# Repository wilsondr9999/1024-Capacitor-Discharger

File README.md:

# Capacitor Discharger

This project is a passive (unpowered) capacitor discharger that can safely discharge capacitors up to 450V and 1000 uF.  It assists the operator in quickly discharging the capacitor and providing visual feedback of the discharging process and its completion.

## Overview

The capacitor discharger is a handheld unit with 2 LEDs for indication, and two standard shrouded test lead ports on one end.  It's purpose is to allow safe discharge of a capacitor that is in-circuit prior to working on that circuit.  Capacitors can hold a charge, sometimes for a long period of time, and in some circuits the amount of energy they can hold is dangerous, even potentially lethal.

This unit allows the operator to touch two test leads to the capacitor terminals, and the unit will allow the capacitor to discharge at a constant rate of 125 mA.  This is sufficient current to discharge the largest capacitor that is recommended to be discharged with this unit (a capacitor rated up to 450V, and up to 1000 uF of capacitance) within about 15 seconds.

## Principle of Operation

The unit is a passive device, i.e. it is not powered and no batteries or power source is needed.  The energy in the capacitor is used to light the indicator LEDs during the discharge.

A fixed resistance bank is used to allow the capacitor to discharge at a constant current of 125 mA.  The capacitor's energy is dumped into 11 resistors rated at 5W each.

One LED (yellow) lights as the capacitor is discharging.  This LED will remain lit until the capacitor has no more energy (usually when it's voltage is less than 2V).

The other LED (red) lights if the capacitor voltage is above 30V.  This LED will extinguish when the capacitor has discharged to less than 30V, indicating that the capacitor would be safe to touch.  An IGBT transistor is used in a specific configuration to drive the >30V LED.

## Instructions for Use

Attach two test leads to the 4mm jacks on the end of the unit.  The unit does not have a polarity restriction, and can discharge capacitors in both orientations.  It is recommended that your test leads are of a type that are rated for at least the working voltage of the capacitor you intend to discharge.  If the voltage is greater than 50V, it is recommended to use high voltage test leads with a category rating of at least CAT I / 600V.

For voltages greater than 50V, use appropriate personal protective equipment (PPE), including electrical safety gloves and safety glasses.

With appropriate personal safety equipment in place, touch the test leads to the capacitor leads in either orientation.  The unit will begin discharging the capacitor, and you will see the yellow discharging LED light up.  The red >30V LED will also light if the capacitor voltage is currently greater than 30V.

Keep the test leads connected to the capacitor until the >30V LED light extinguished.  Once the >30V LED light is extinguished, the capacitor is safe to work with.  If the work requires as close to zero charge in the capacitor as possible, continue holding the test leads connected to the capacitor until the discharge LED light is dim or extinguished.

## Assembly

Gerber files are available in the [1024 Capacitor Discharger](KiCAD%20Project%20-%20Discharger/Fabrication%20Exports/1024%20Capacitor%20Discharger.zip) folder.  The [1024 Capacitor Discharger](KiCAD%20Project%20-%20Discharger/Fabrication%20Exports/1024%20Capacitor%20Discharger.zip) file is a pre-compressed archive that is ready to upload to Oshpark.

All parts needed are listed in the [BOM](KiCAD%20Project%20-%20Discharger/BOM/BOM%201024%20Capacitor%20Discharger.csv) CSV file.

If you want to use a solder stencil for reflow of the SMD components, Osh Stencils can produce this stencil from the [1024 Capacitor Discharger-F_Paste](KiCAD%20Project%20-%20Discharger/Fabrication%20Exports/1024%20Capacitor%20Discharger-F_Paste.gbr) Gerber file.  Select a Stainless Steel 4 mil stencil with a border size of 0.75 inches.  The Solder Stencil Jig is designed to fit this stencil.

Use the [SSJv2 1024 Capacitor Discharger](FreeCAD%20Project/Solder%20Stencil%20Jig%20V2/SSJv2%201024%20Capacitor%20Discharger.stl) file to print the solder stencil jig.  A .3mf file is included if you use PrusaSlicer.  Otherwise use the .stl file with the following settings:

- 0.2 mm layer height
- 3 perimeters
- 4 solid layers on bottom
- 5 solid layers on top
- 20% infill
- No supports required

Solder the SMD components onto the PCB using the stencil + solder paste + reflow, or hand solder them.

Solder the THT components onto the PCB by hand.  Be careful when bending the IGBT legs, they need to be accurate because the hole in the TO-220 case must align with the heat sink and the hole in the PCB.  It is recommended to solder the 4mm PCB-mount Banana jacks while the board is fitted into the case top.  This will ensure that the Banana jacks are perfectly aligned and will not impede the fitting of the PCB in the case.

There is a [ResistorBender](FreeCAD%20Project/1024%20Capacitor%20Discharger%20Case/ResistorBender.stl) file in the 1024 Capacitor Discharge Case directory, this can be optionally printed to properly and uniformly bend the resistor legs to fit the PCB.

When assembling the IGBT heat sink, the stackup should be (from the top down):

- M3x8 button-head screw
- Screw insulator
- TO-220 IGBT
- Thermal grease/compound
- Mica insulator sheet from the TO-220 mounting kit listed in the BOM
- Thermal grease/compound
- Aluminum heat sink
- PCB
- (Back of PCB) Flat Washer
- (Back of PCB) M3 hex nut

The screw that is supplied with the TO-220 mounting kit is too long to fit properly in the printed case.  Replace this screw and nut with a button head M3x8 screw, and use the flat washer and an M3 hex nut on the back of the PCB.  Do not use the lock washer.  This should clear the printed case when assembled.

The Mica insulator sheet may be slightly too large to fit inside the aluminum heat sink.  It can be trimmed with scissors.

Use the [CaseBottom](FreeCAD%20Project/1024%20Capacitor%20Discharger%20Case/CaseBottom.stl) and [CaseTop](FreeCAD%20Project/1024%20Capacitor%20Discharger%20Case/CaseTop.stl) files to print the case, using the same settings as the solder stencil jig.  Use a soldering iron to insert 4 Heat-Set Inserts into the case top.  The Heat-Set Inserts should be an M3 x 6mm size.  The screws used to assembly the case should be an M3x12 with a hex cap head.

Assemble the case halves together with the PCB inside, and insert the 4 hex cap M3x12 screws and tighten.

## License

This project is licensed under two restrictive licenses:

The hardware design is licensed under the CERN Open Hardware Licence Version 2 - Strongly Reciprocal.

The documentation, images, and instructions are licensed under the Creative Commons Attribution-ShareAlike 4.0 International Public License.

As stated by the licenses, all uses of this project require attribution and require open-source release under the same licenses.

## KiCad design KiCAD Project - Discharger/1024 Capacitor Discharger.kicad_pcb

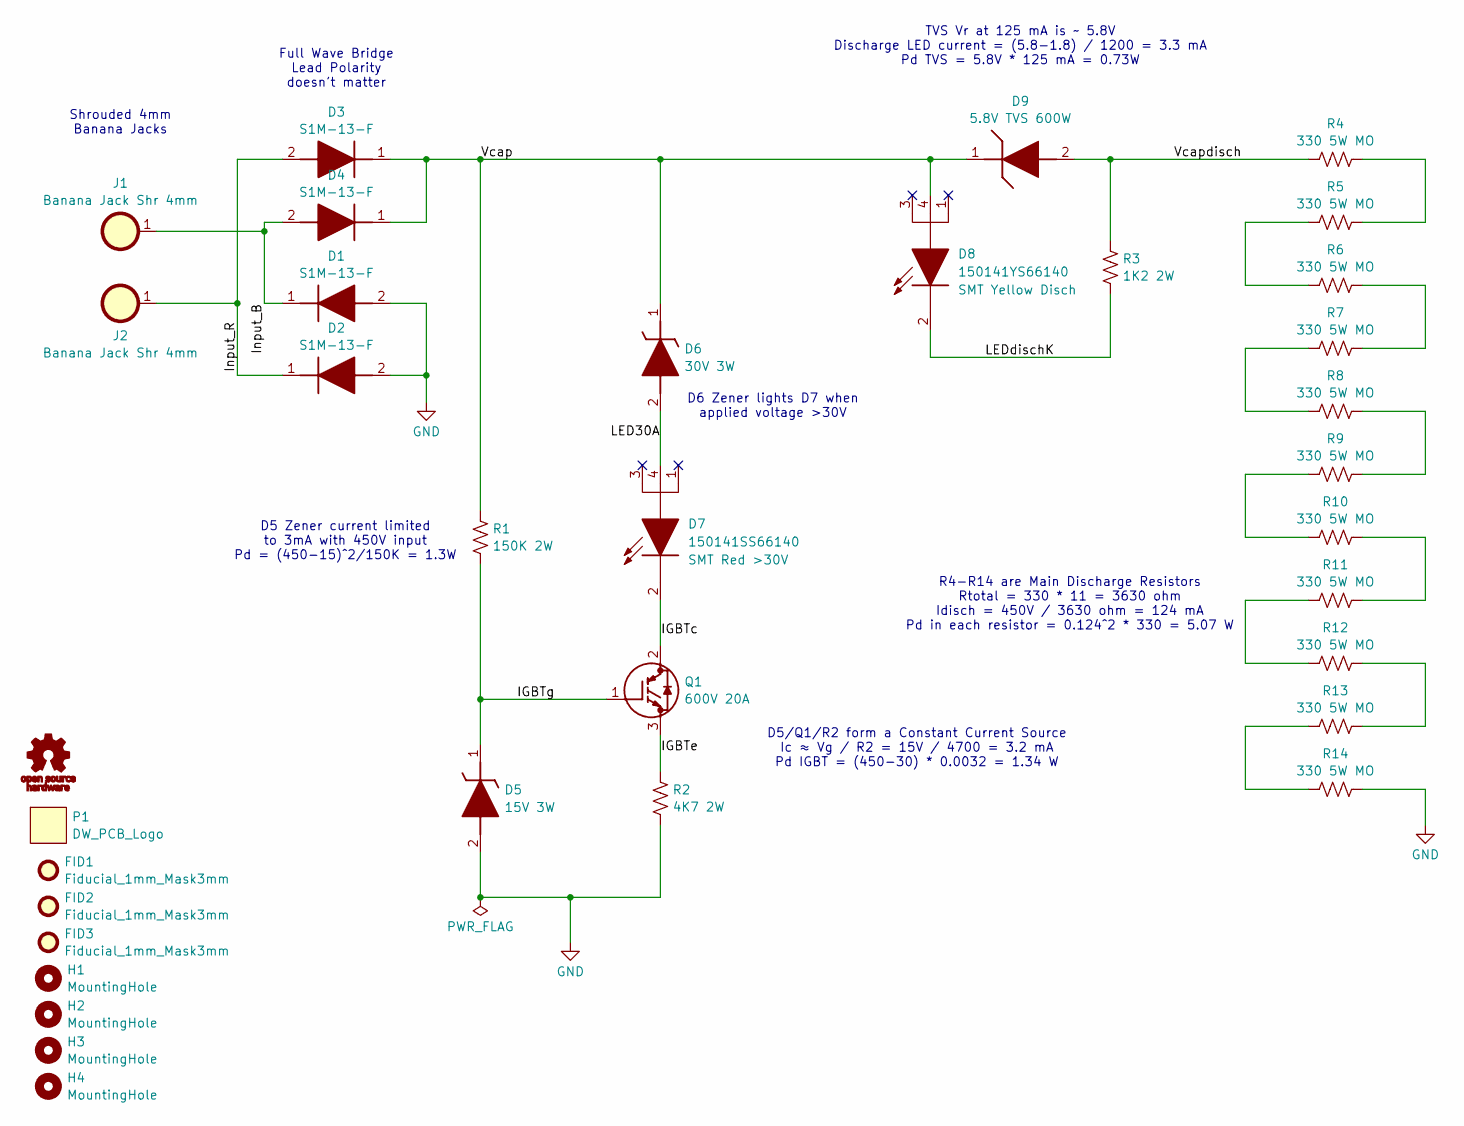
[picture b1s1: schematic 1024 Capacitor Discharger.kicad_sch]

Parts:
D1, D2, D3, D4: S1M-13-F; [D] Diodes Inc S1M-F; Mouser Part Number 621-S1M-F
D5: 1SMB5929BT3G; [D] OnSemi Zener DIOM5436X247N; Mouser Part Number 863-1SMB5929BT3G
D6: 1SMB5936BT3G; [D] OnSemi Zener DIOM5436X247N; Mouser Part Number 863-1SMB5936BT3G
D7: 150141SS66140; [D] Wurth Elektronik 150141SS66140; Mouser Part Number 710-150141SS66140
D8: 150141YS66140; [D] Wurth Elektronik 150141SS66140; Mouser Part Number 710-150141YS66140
D9: 5.8V TVS 600W; [D] Nexperia TVS UniDir PMEG3050EP115; Mouser Part Number 771-PTVS3V3P1UTP,115
FID1, FID2, FID3: Fiducial_1mm_Mask3mm
G1: OSHW_Logo
H1, H2, H3, H4: MountingHole; MountingHole_3.2mm_M3
J1, J2: Banana Jack Shr 4mm; [J] CalTestElec CT3151SP-X; Manufacturer_Part_Number CT3151SP-X; Mouser Part Number 510-CT3151SP-4
P1: DW_PCB_Logo
Q1: 600V 20A; [Q] Infineon IKP20N60T IGBT with ATS-PCB1069 Heat Sink; Mouser Part Number 726-IKP20N60T
R1: 150K 2W; R_2512_6332Metric; Manufacturer_Part_Number CRGP2512F150K; Mouser Part Number 279-CRGP2512F150K
R2: 4K7 2W; R_2512_6332Metric; Manufacturer_Part_Number CRGP2512F4K7; Mouser Part Number 279-CRGP2512F4K7
R3: 1K2 2W; R_2512_6332Metric; Manufacturer_Part_Number CRGP2512F1K2; Mouser Part Number 279-CRGP2512F1K2
R4, R5, R6, R7, R8, R9, R10, R11, R12, R13, R14: 330 5W MO; [R] TE Connectivity MO Res 5W; Manufacturer_Part_Number ROX5SSJ330R; Mouser Part Number 279-ROX5SSJ330R

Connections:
/IGBTc: D7.2 (K), Q1.2 (C)
/IGBTe: Q1.3 (E), R2.1
/IGBTg: D5.1 (K), Q1.1 (G), R1.2
/Input_B: D1.1 (K), D4.2 (A), J1.1
/Input_R: D2.1 (K), D3.2 (A), J2.1
/LED30A: D6.2 (A), D7.4 (A2)
/LEDdischK: D8.2 (K), R3.2
/Vcap: D3.1 (K), D4.1 (K), D6.1 (K), D8.4 (A2), D9.1 (K), R1.1
/Vcapdisch: D9.2 (A), R3.1, R4.1
GND: D1.2 (A), D2.2 (A), D5.2 (A), R2.2, R14.2
unnamed: R4.2, R5.2
unnamed: R5.1, R6.1
unnamed: R6.2, R7.2
unnamed: R7.1, R8.1
unnamed: R8.2, R9.2
unnamed: R9.1, R10.1
unnamed: R10.2, R11.2
unnamed: R11.1, R12.1
unnamed: R12.2, R13.2
unnamed: R13.1, R14.1

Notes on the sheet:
Full Wave Bridge Lead Polarity doesn't matter
R4-R14 are Main Discharge Resistors Rtotal = 330 * 11 = 3630 ohm Idisch = 450V / 3630 ohm = 124 mA Pd in each resistor = 0.124^2 * 330 = 5.07 W
TVS Vr at 125 mA is ~ 5.8V Discharge LED current = (5.8-1.8) / 1200 = 3.3 mA Pd TVS = 5.8V * 125 mA = 0.73W
D5/Q1/R2 form a Constant Current Source Ic ≈ Vg / R2 = 15V / 4700 = 3.2 mA Pd IGBT = (450-30) * 0.0032 = 1.34 W
Shrouded 4mm Banana Jacks
D6 Zener lights D7 when applied voltage >30V
D5 Zener current limited to 3mA with 450V input Pd = (450-15)^2/150K = 1.3W

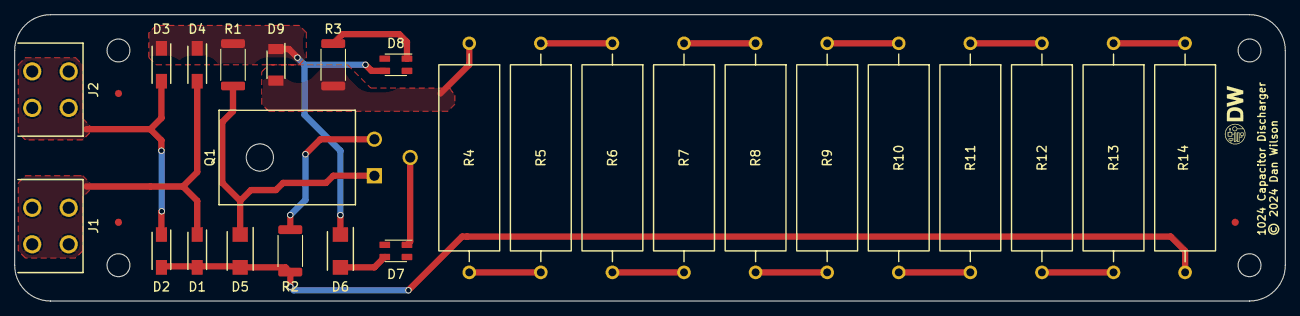
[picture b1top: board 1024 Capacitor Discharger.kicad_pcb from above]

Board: 2 copper layers, 177.5 x 40.0 mm, 35 parts (1 on the bottom side), 20 nets.

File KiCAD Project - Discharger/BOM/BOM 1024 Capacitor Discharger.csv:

"Reference","Value","Datasheet","Footprint","Qty","DNP","Height","Manufacturer_Name","Manufacturer_Part_Number","Mouser Part Number","Mouser Price/Stock","Description"
"D1,D2,D3,D4","S1M-13-F","https://www.mouser.com/datasheet/2/115/DIOD_S_A0007810797_1-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","DW_Semiconductors:[D] Diodes Inc S1M-F","4","","2.4","Diodes Incorporated","S1M-13-F","621-S1M-F","https://www.mouser.com/ProductDetail/Diodes-Incorporated/S1M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","Diode Standard 1A 1000V SMA Diodes Inc S1M-13-F, SMT Diode, 1000V 1A, 3us, 2-Pin DO-214AC"
"D5","1SMB5929BT3G","https://www.mouser.com/datasheet/2/308/1SMB5913BT3_D-2309637.pdf","DW_Semiconductors:[D] OnSemi Zener DIOM5436X247N","1","","2.47","onsemi","1SMB5929BT3G","863-1SMB5929BT3G","https://www.mouser.com/ProductDetail/onsemi/1SMB5929BT3G?qs=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","15V 3W"
"D6","1SMB5936BT3G","https://www.mouser.com/datasheet/2/308/1SMB5913BT3_D-2309637.pdf","DW_Semiconductors:[D] OnSemi Zener DIOM5436X247N","1","","2.47","onsemi","1SMB5936BT3G","863-1SMB5936BT3G","https://www.mouser.com/ProductDetail/onsemi/1SMB5936BT3G?qs=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","30V 3W"
"D7","150141SS66140","https://www.we-online.com/components/products/datasheet/1501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","DW_Optoelectronics:[D] Wurth Elektronik 150141SS66140","1","","3.27","Wurth Elektronik","150141SS66140","710-150141SS66140","https://www.mouser.com/ProductDetail/Wurth-Elektronik/150141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","SMT Red >30V"
"D8","150141YS66140","https://www.we-online.com/components/products/datasheet/1501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","DW_Optoelectronics:[D] Wurth Elektronik 150141SS66140","1","","3.27","Wurth Elektronik","150141YS66140","710-150141YS66140","https://www.mouser.com/ProductDetail/Wurth-Elektronik/150141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","SMT Yellow Disch"
"D9","5.8V TVS 600W","https://assets.nexperia.com/documents/data-sheet/PTVSXP1UTP_SER.pdf","DW_Semiconductors:[D] Nexperia TVS UniDir PMEG3050EP115","1","","1","Nexperia","PTVS3V3P1UTP,115","771-PTVS3V3P1UTP,115","https://www.mouser.com/ProductDetail/Nexperia/PTVS3V3P1UTP11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","PTVSxP1UTP series - High-temperature 600 W Transient Voltage Suppressor 8V Clamp"
"J1,J2","Banana Jack Shr 4mm","https://www.mouser.com/datasheet/2/701/P315100_rJ_2c_4mm_She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","DW_Connectors:[J] CalTestElec CT3151SP-X","2","","13.1","Cal Test Electronics","CT3151SP-X","510-CT3151SP-4","https://www.mouser.com/ProductDetail/Cal-Test/CT3151SP-4?qs=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","4mm Sheath Banana Jacks (Sockets), PCB Mount"
"Q1","600V 20A","https://www.mouser.com/datasheet/2/196/Infineon_IKP20N60T_DS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","DW_Semiconductors:[Q] Infineon IKP20N60T IGBT with ATS-PCB1069 Heat Sink","1","","4.6","Infineon","IKP20N60T","726-IKP20N60T","https://www.mouser.com/ProductDetail/Infineon-Technologies/I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","Infineon IKP20N60T, IGBT Transistor, 20 A 600 V, TO-220-3"
"R1","150K 2W","https://www.mouser.com/datasheet/2/418/9/ENG_DS_9_1773463_9_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","Resistor_SMD:R_2512_6332Metric","1","","0.65","TE Connectivity","CRGP2512F150K","279-CRGP2512F150K","https://www.mouser.com/ProductDetail/TE-Connectivity-Holswor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","Resistor SMD 2512 150K 2W 500V"
"R2","4K7 2W","https://www.mouser.com/datasheet/2/418/9/ENG_DS_9_1773463_9_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","Resistor_SMD:R_2512_6332Metric","1","","0.65","TE Connectivity","CRGP2512F4K7","279-CRGP2512F4K7","https://www.mouser.com/ProductDetail/TE-Connectivity-Holswor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","Resistor SMD 2512 4K7 2W 500V"
"R3","1K2 2W","https://www.mouser.com/datasheet/2/418/9/ENG_DS_9_1773463_9_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","Resistor_SMD:R_2512_6332Metric","1","","0.65","TE Connectivity","CRGP2512F1K2","279-CRGP2512F1K2","https://www.mouser.com/ProductDetail/TE-Connectivity-Holswor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","Resistor SMD 2512 1K2 2W 500V"
"R4,R5,R6,R7,R8,R9,R10,R11,R12,R13,R14","330 5W MO","https://www.mouser.com/datasheet/2/418/9/ENG_DS_1773271_J-15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","DW_Passives:[R] TE Connectivity MO Res 5W","11","","12","TE Connectivity","ROX5SSJ330R","279-ROX5SSJ330R","https://www.mouser.com/ProductDetail/TE-Connectivity-Holswor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","Metal Oxide Film Resistor, 5W, 750V"

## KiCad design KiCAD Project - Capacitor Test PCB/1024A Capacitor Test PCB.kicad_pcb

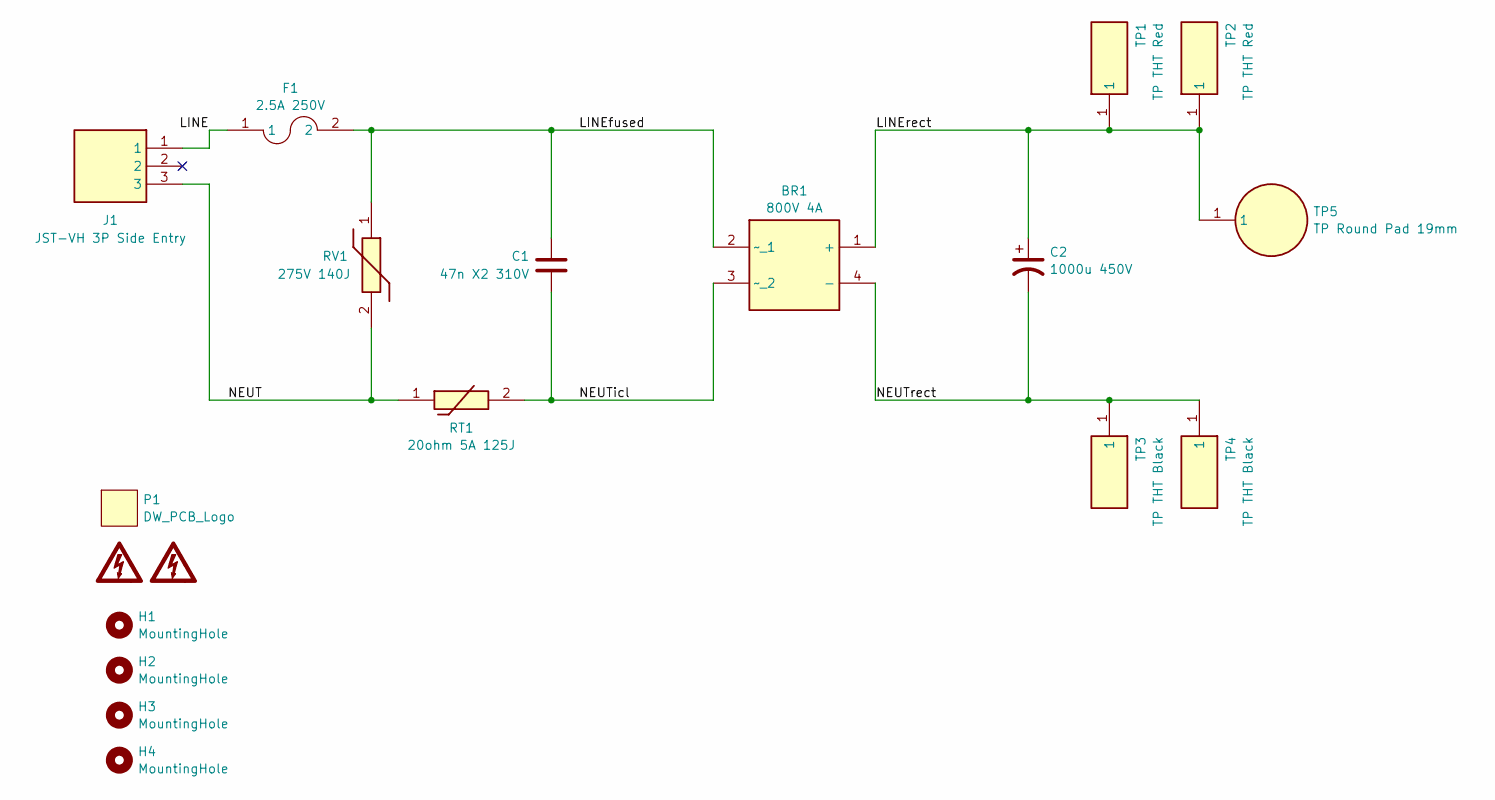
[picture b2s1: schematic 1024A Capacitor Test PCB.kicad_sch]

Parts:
BR1: 800V 4A; [BR] Vishay 800V 4A Bridge Rectifier GBL08EE3P; Mouser Part Number 78-GBL08E-E3/P
C1: 47n X2 310V; [C] Kemet Film Cap 47n 310V X2; Manufacturer_Part_Number F861KM473M310C; Mouser Part Number 80-F861KM473M310C
C2: 1000u 450V; [C] Kemet ALC70C102EH450 Al Elec Cap 450V 1000uF; Manufacturer_Part_Number ALC70C102EH450; Mouser Part Number 80-ALC70C102EH450
F1: 2.5A 250V; [F] Littelfuse TE5-372; Mouser Part Number 576-39212500440
G1, G2: High_Voltage_6.5mm
H1, H2, H3, H4: MountingHole; MountingHole_3.2mm_M3
J1: JST-VH 3P Side Entry; [J] JST-VN 3P Side Entry; Manufacturer_Part_Number B3PS-VH; Digikey Part Number 455-B3PS-VH-ND
P1: DW_PCB_Logo
RT1: 20ohm 5A 125J; [RT] Ametherm SL22 20005 ICL; Mouser Part Number 995-SL22-20005
RV1: 275V 140J; [RV] Littelfuse MOV V275LA40AP; Mouser Part Number 576-V275LA40AP
TP1, TP2: TP THT Red; [TP] Keystone Elec TP THT 5005 Red; Mouser Part Number 534-5005
TP3, TP4: TP THT Black; [TP] Keystone Elec TP THT 5006 Black; Mouser Part Number 534-5006
TP5: TP Round Pad 19mm; [TP] Round Pad for Test Lead

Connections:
/LINE: F1.1, J1.1
/LINEfused: BR1.2 (~_1), C1.1, F1.2, RV1.1
/LINErect: BR1.1 (+), C2.1, TP1.1, TP2.1, TP5.1
/NEUT: J1.3, RT1.1, RV1.2
/NEUTicl: BR1.3 (~_2), C1.2, RT1.2
/NEUTrect: BR1.4 (-), C2.2, TP3.1, TP4.1

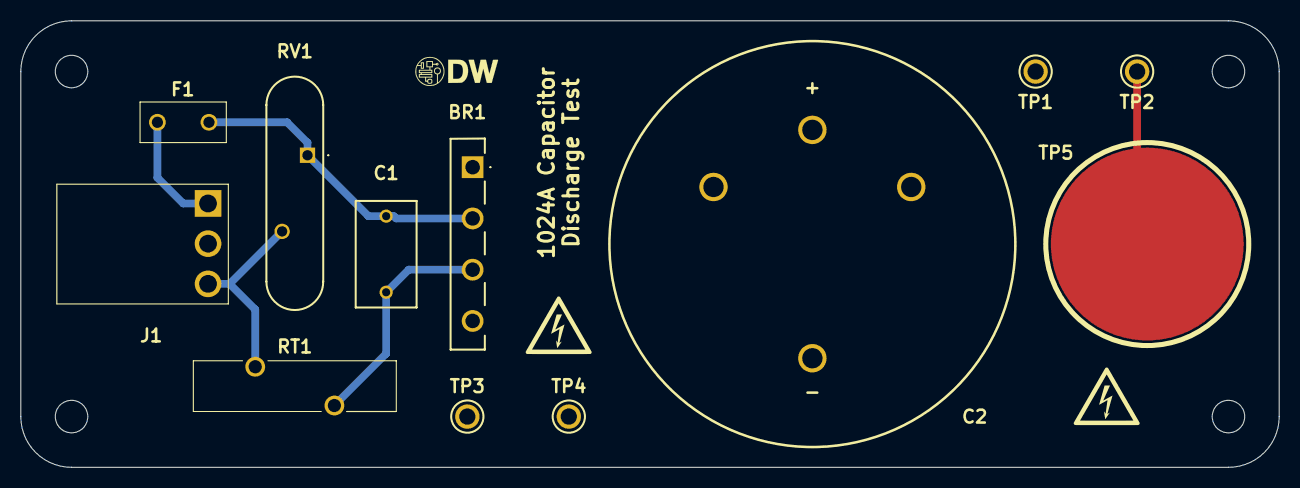
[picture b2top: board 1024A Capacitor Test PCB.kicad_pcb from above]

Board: 2 copper layers, 124.0 x 44.0 mm, 19 parts (0 on the bottom side), 6 nets.

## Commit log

2024-08-17 Add README
2024-08-30 v1.0.0.0 - Release
    Release version of the capacitor discharger.
2024-08-30 v1.0.0.1 - Release
2024-08-30 v1.0.0.2 - Release

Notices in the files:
KiCAD Project - Capacitor Test PCB/1024A Capacitor Test PCB.kicad_sch:
Copyright © 2024 Dan Wilson
KiCAD Project - Discharger/1024 Capacitor Discharger.kicad_pcb:
This hardware is licensed under the CERN
Open Hardware License - Strongly Reciprocal (CERN-OHL-S-2.0).
This work is Copyrighted © 2024 by Dan Wilson, all rights reserved.
The work is licensed for use only under the terms set forth in the
CERN-OHL-S-2.0 license.  Any use, modification, or redistribution
must comply with the terms of the CERN-OHL-S-2.0 license.
